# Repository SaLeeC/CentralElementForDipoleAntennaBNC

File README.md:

# Central Element For Dipole Antenna BNC

# Central Element For Dipole Antenna with a BNC connector

This dipole core is designed for use with a BNC connector with 4 screw holes. The element is composed of two pieces laser cut from a 3mm Plexiglass sheet. The two pieces have been glued together to increase their mechanical strength.

The connector is connected to two rings consisting of 5 screws each. The central screw is for connecting the connector (hot pole and GND) and the 4 peripheral screws are used to connect up to 4 different dipoles.

The project was created with FreeCad (19.x) and the folder contains the .DXF files ready for laser cutting

# Elemento centrale per antenna a dipolo con connettore BNC

Questo nucleo dipolo è progettato per l'uso con un connettore BNC con 4 fori per le viti. L'elemento è composto da due pezzi tagliati al laser da una lastra di plexiglass da 3 mm. I due pezzi sono stati incollati tra loro per aumentarne la resistenza meccanica.

Il connettore è collegato a due anelli composti da 5 viti ciascuno. La vite centrale serve per il collegamento del connettore (polo caldo e GND) e le 4 viti periferiche servono per collegare fino a 4 dipoli differenti. 

Il progetto è stato creato con FreeCad (19.x) e la cartella contiene i file .DXF pronti per il taglio laser

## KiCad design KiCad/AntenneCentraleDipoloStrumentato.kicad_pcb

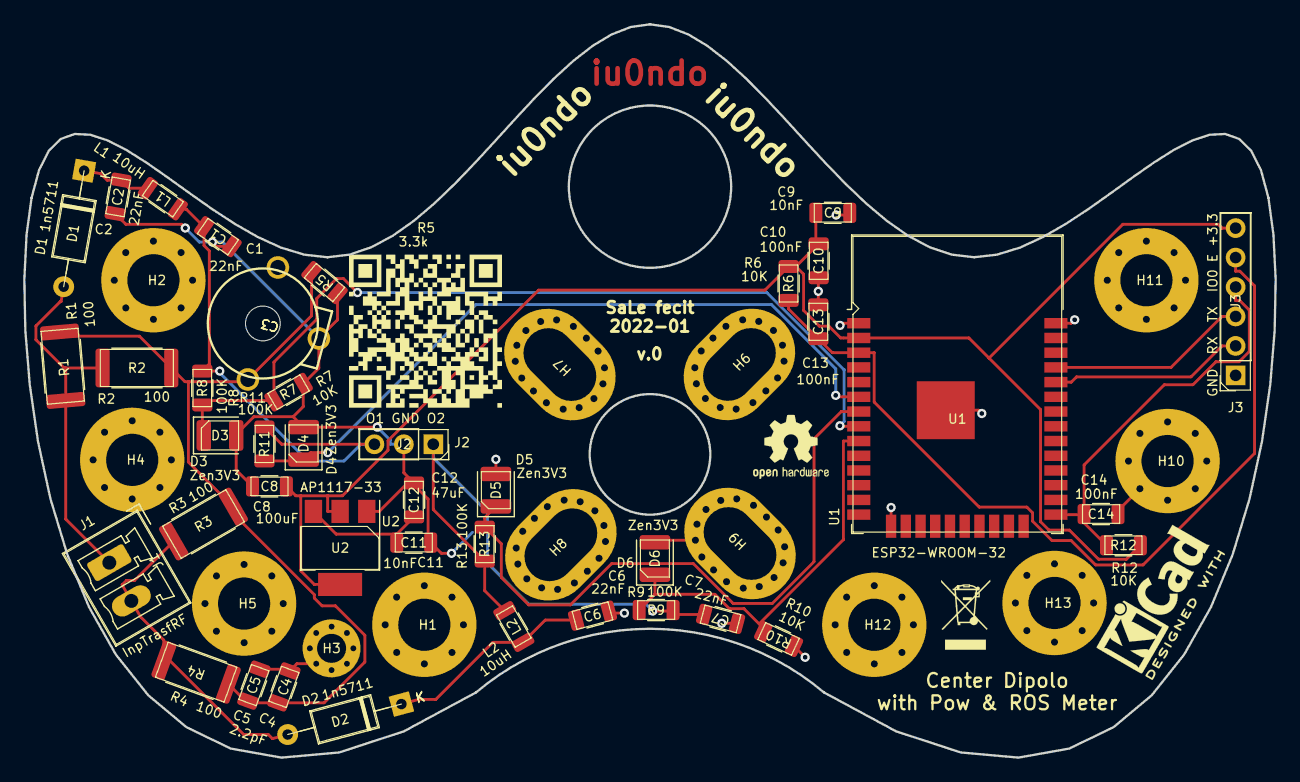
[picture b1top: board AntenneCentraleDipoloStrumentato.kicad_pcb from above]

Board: 2 copper layers, 107.9 x 63.2 mm, 54 parts (0 on the bottom side), 19 nets.

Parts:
C1, C2, C6, C7: 22nF; R_1206_3216Metric
C3: C_Trim; GZC10100
C4, C5: 2.2pF; R_1206_3216Metric
C8: 100uF; R_1206_3216Metric
C9, C11: 10nF; R_1206_3216Metric
C10, C13, C14: 100nF; R_1206_3216Metric
C12: 47uF; R_1206_3216Metric
D1, D2: 1n5711; D_A-405_P10.16mm_Horizontal
D3, D4, D5, D6: Zen3V3; D_1210_3225Metric
H1, H2, H4, H5, H10, H11, H12, H13: MountingHole_4.5mm_Pad_Via
H3: MountingHole_2.5mm_Pad_Via
H6, H7, H8, H9: MountingHole_4.3x7mm_M4_Pad_Via
J1: InpTrasfRF; PhoenixContact_MCV_1,5_2-G-3.81_1x02_P3.81mm_Vertical
J2: O1 GND O2; PinSocket_1x03_P2.54mm_Vertical
J3: GND RX TX IO0 E +3.3; PinSocket_1x06_P2.54mm_Vertical
L1, L2: 10uH; L_1206_3216Metric
QR0001: github.com/SaLeeC/CentralElementForDipoleAntennaB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; //github.com/SaLeeC/CentralElementForDipoleAntennaBNC
R1, R2, R3, R4: 100; R_2512_6332Metric
R5: 3.3k; R_1206_3216Metric
R6, R7, R10, R12: 10K; R_1206_3216Metric
R8, R9, R11, R13: 100K; R_1206_3216Metric
U1: ESP32-WROOM-32
U2: AP1117-33; SOT-223-3_TabPin2

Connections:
GND: C1.1, C2.1, C3.2, C6.1, C7.1, C8.1, C9.1, C10.1, C11.1, C12.1, C13.1, C14.1, D3.2 (A), D4.2 (A), D5.2 (A), D6.2 (A), H6.1, H7.1, H8.1, H9.1, H10.1, H11.1, H12.1, H13.1, J2.2, J3.1, R5.1, R7.1, R10.1, U1.1 (GND), U1.15 (GND), U1.38 (GND), U1.39 (GND), U2.1 (GND)
unnamed: C1.2, J2.3, L1.1, R8.1, R11.2
unnamed: C2.2, D1.1 (K), L1.2
unnamed: C3.1, C4.1, C5.1, R1.2, R2.2, R3.1, R4.1, R5.2
unnamed: C4.2, C5.2, H1.1, H2.1, H3.1, H4.1, H5.1
unnamed: C6.2, D2.1 (K), L2.1
unnamed: C7.2, J2.1, L2.2, R9.2, R13.1
unnamed: C8.2, C9.2, C10.2, J3.6, R6.2, R12.2, U1.2 (VDD), U2.2 (VO)
unnamed: C11.2, C12.2, U2.3 (VI)
unnamed: C13.2, J3.5, R6.1, U1.3 (EN)
unnamed: C14.2, J3.4, R12.1, U1.25 (IO0)
unnamed: D1.2 (A), J1.1, R1.1, R2.1
unnamed: D2.2 (A), J1.2, R3.2, R4.2
unnamed: D3.1 (K), R7.2, R8.2, U1.8 (IO32)
unnamed: D4.1 (K), R11.1, U1.6 (IO34)
unnamed: D5.1 (K), R13.2, U1.7 (IO35)
unnamed: D6.1 (K), R9.1, R10.2, U1.9 (IO33)
unnamed: J3.2, U1.34 (RXD0/IO3)
unnamed: J3.3, U1.35 (TXD0/IO1)
